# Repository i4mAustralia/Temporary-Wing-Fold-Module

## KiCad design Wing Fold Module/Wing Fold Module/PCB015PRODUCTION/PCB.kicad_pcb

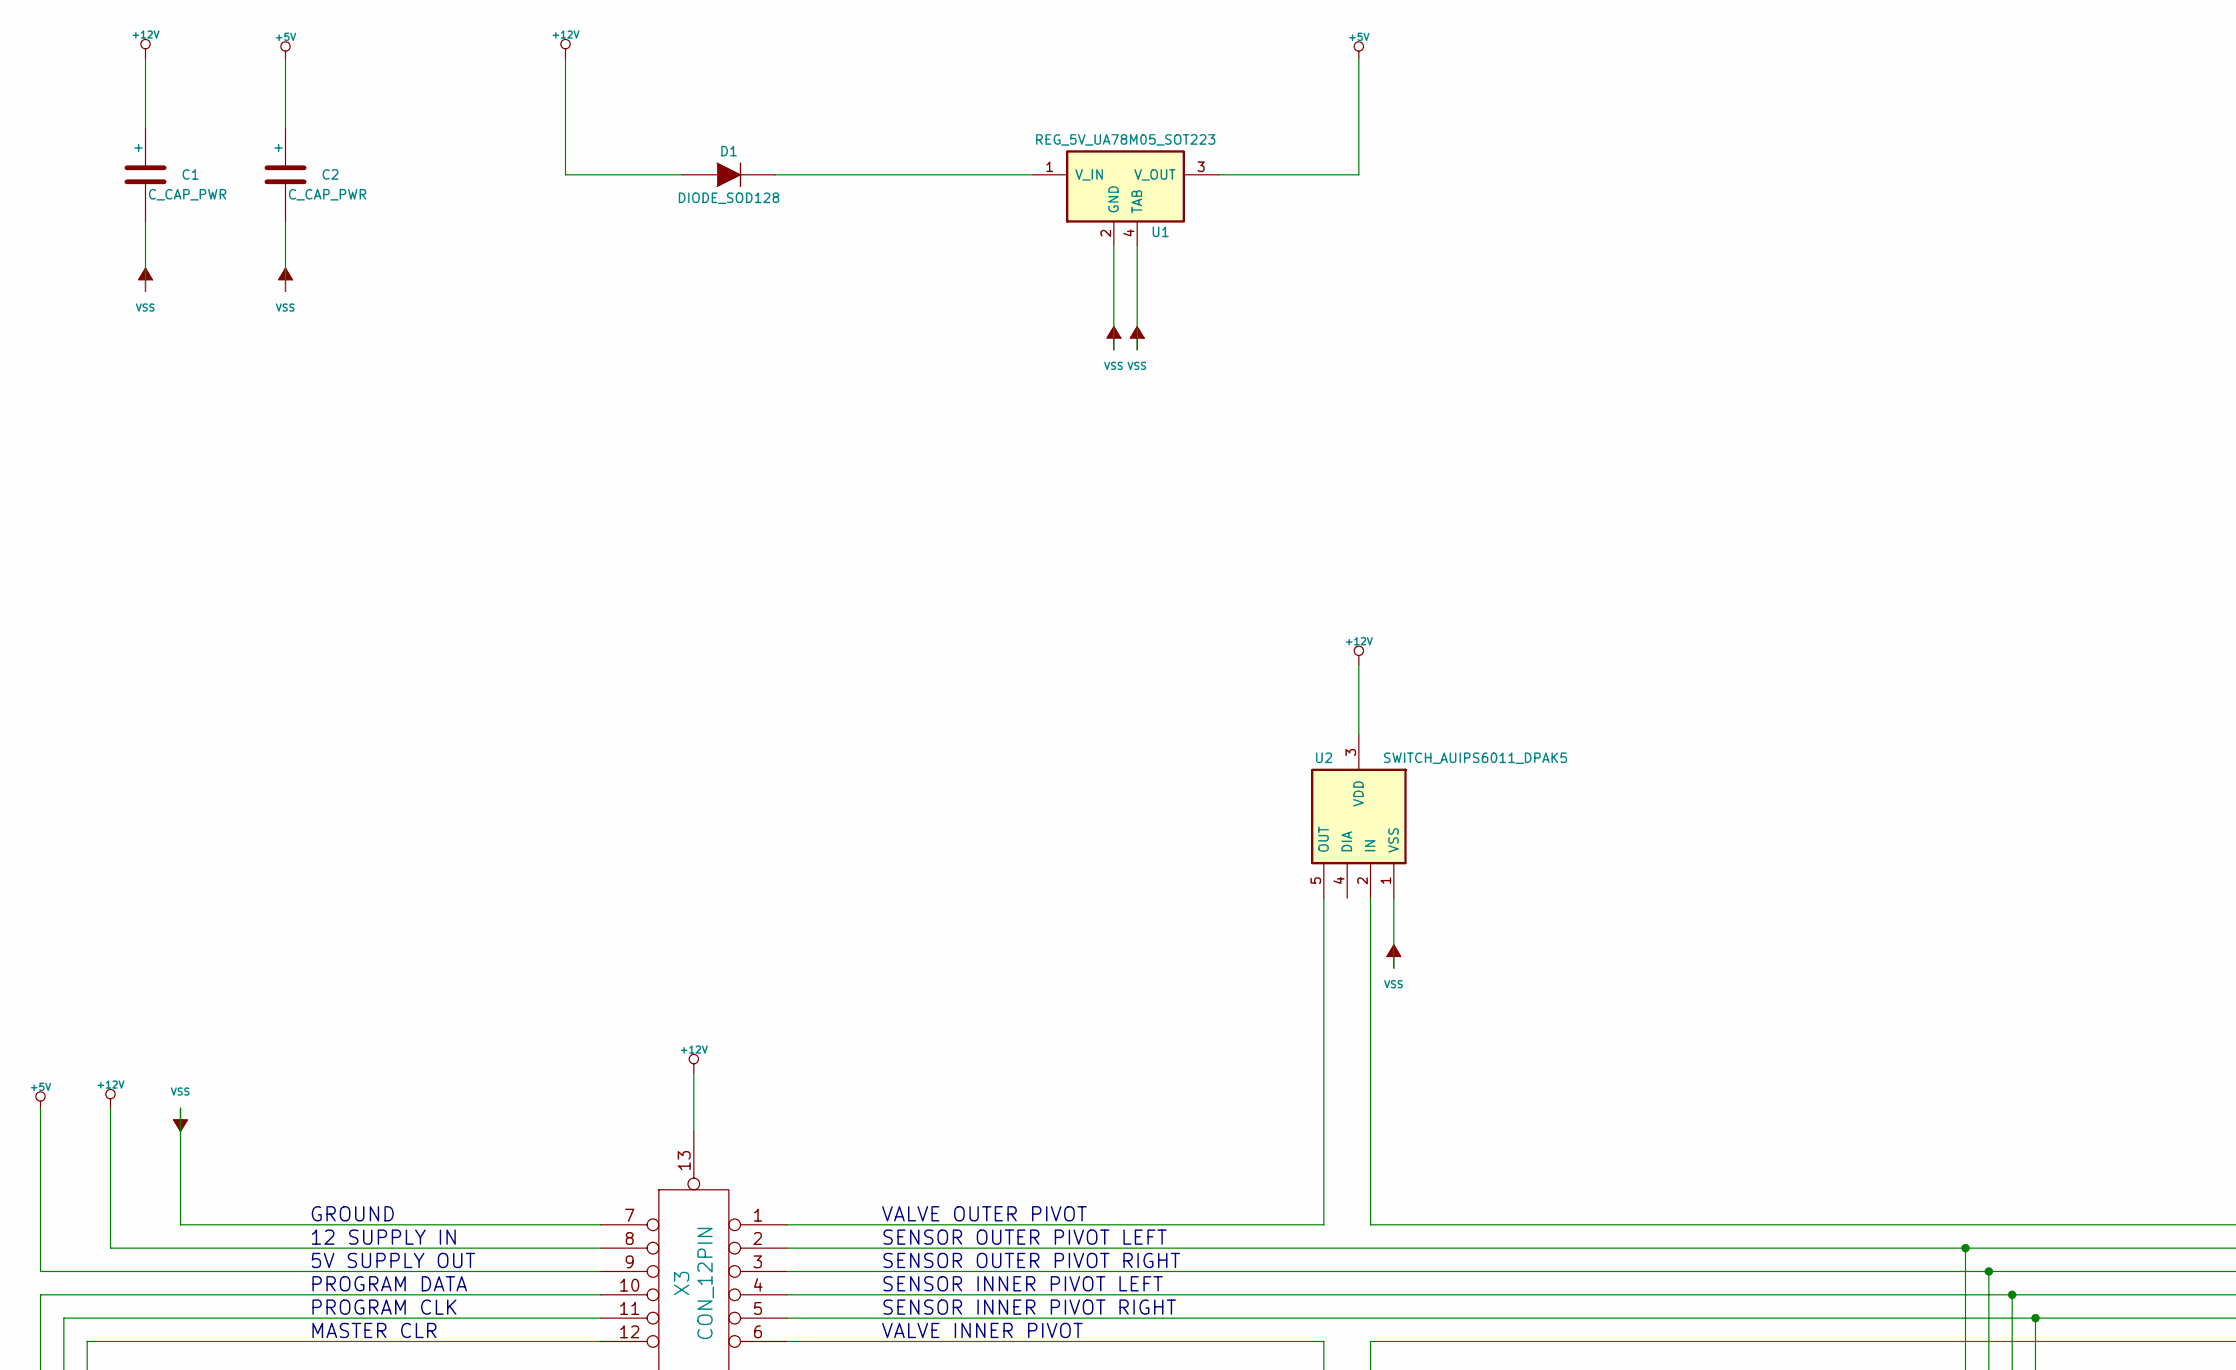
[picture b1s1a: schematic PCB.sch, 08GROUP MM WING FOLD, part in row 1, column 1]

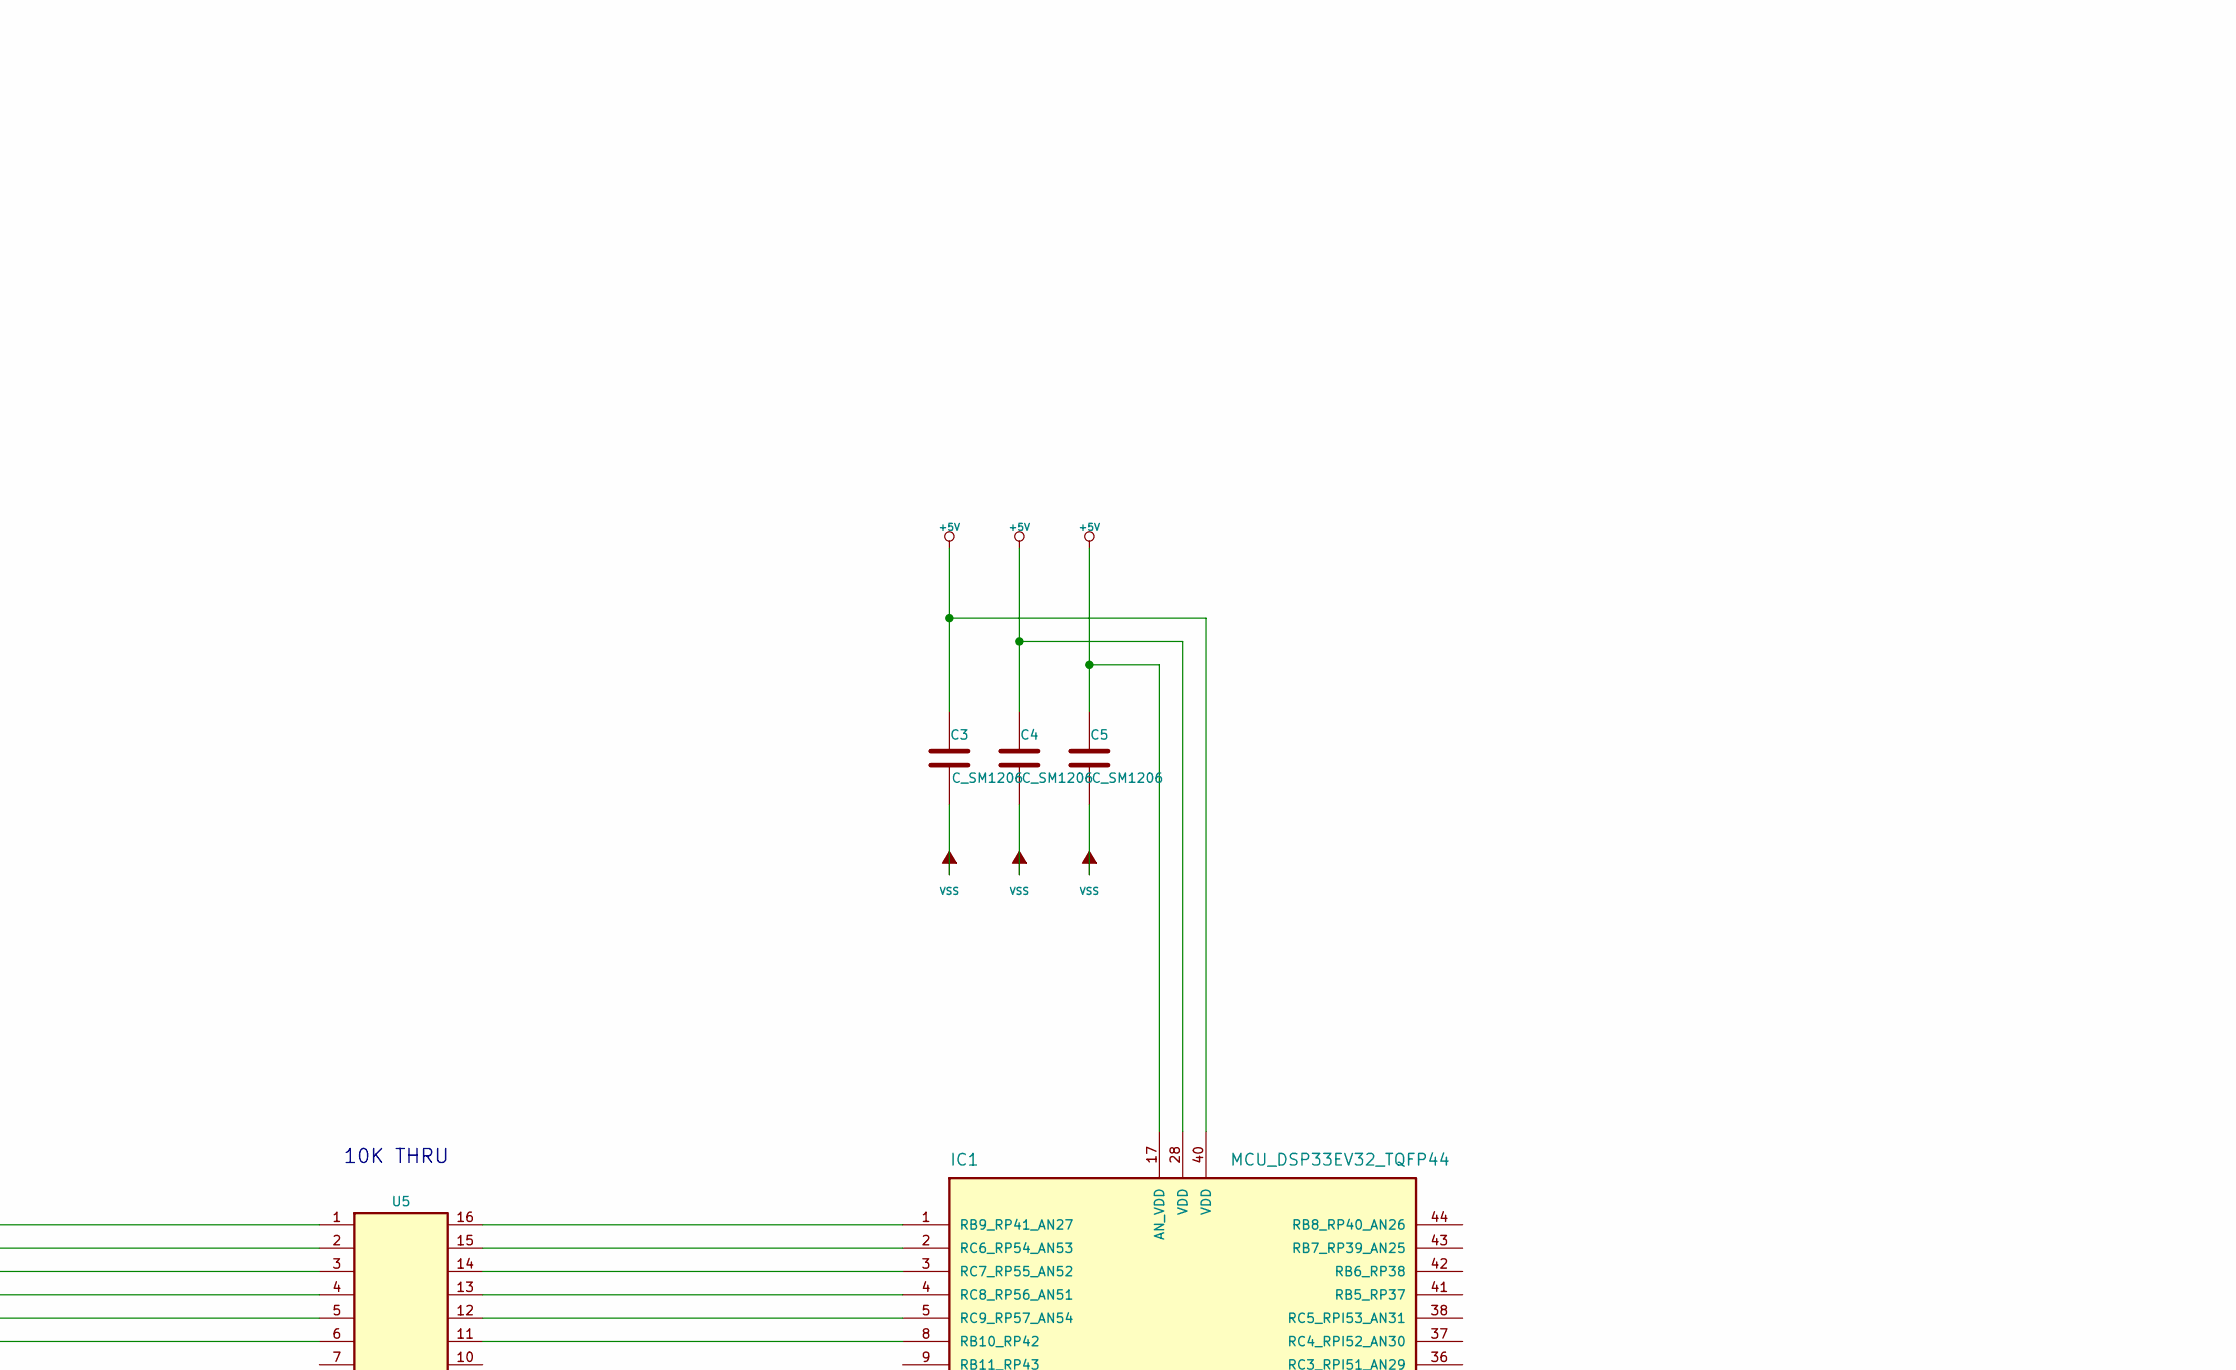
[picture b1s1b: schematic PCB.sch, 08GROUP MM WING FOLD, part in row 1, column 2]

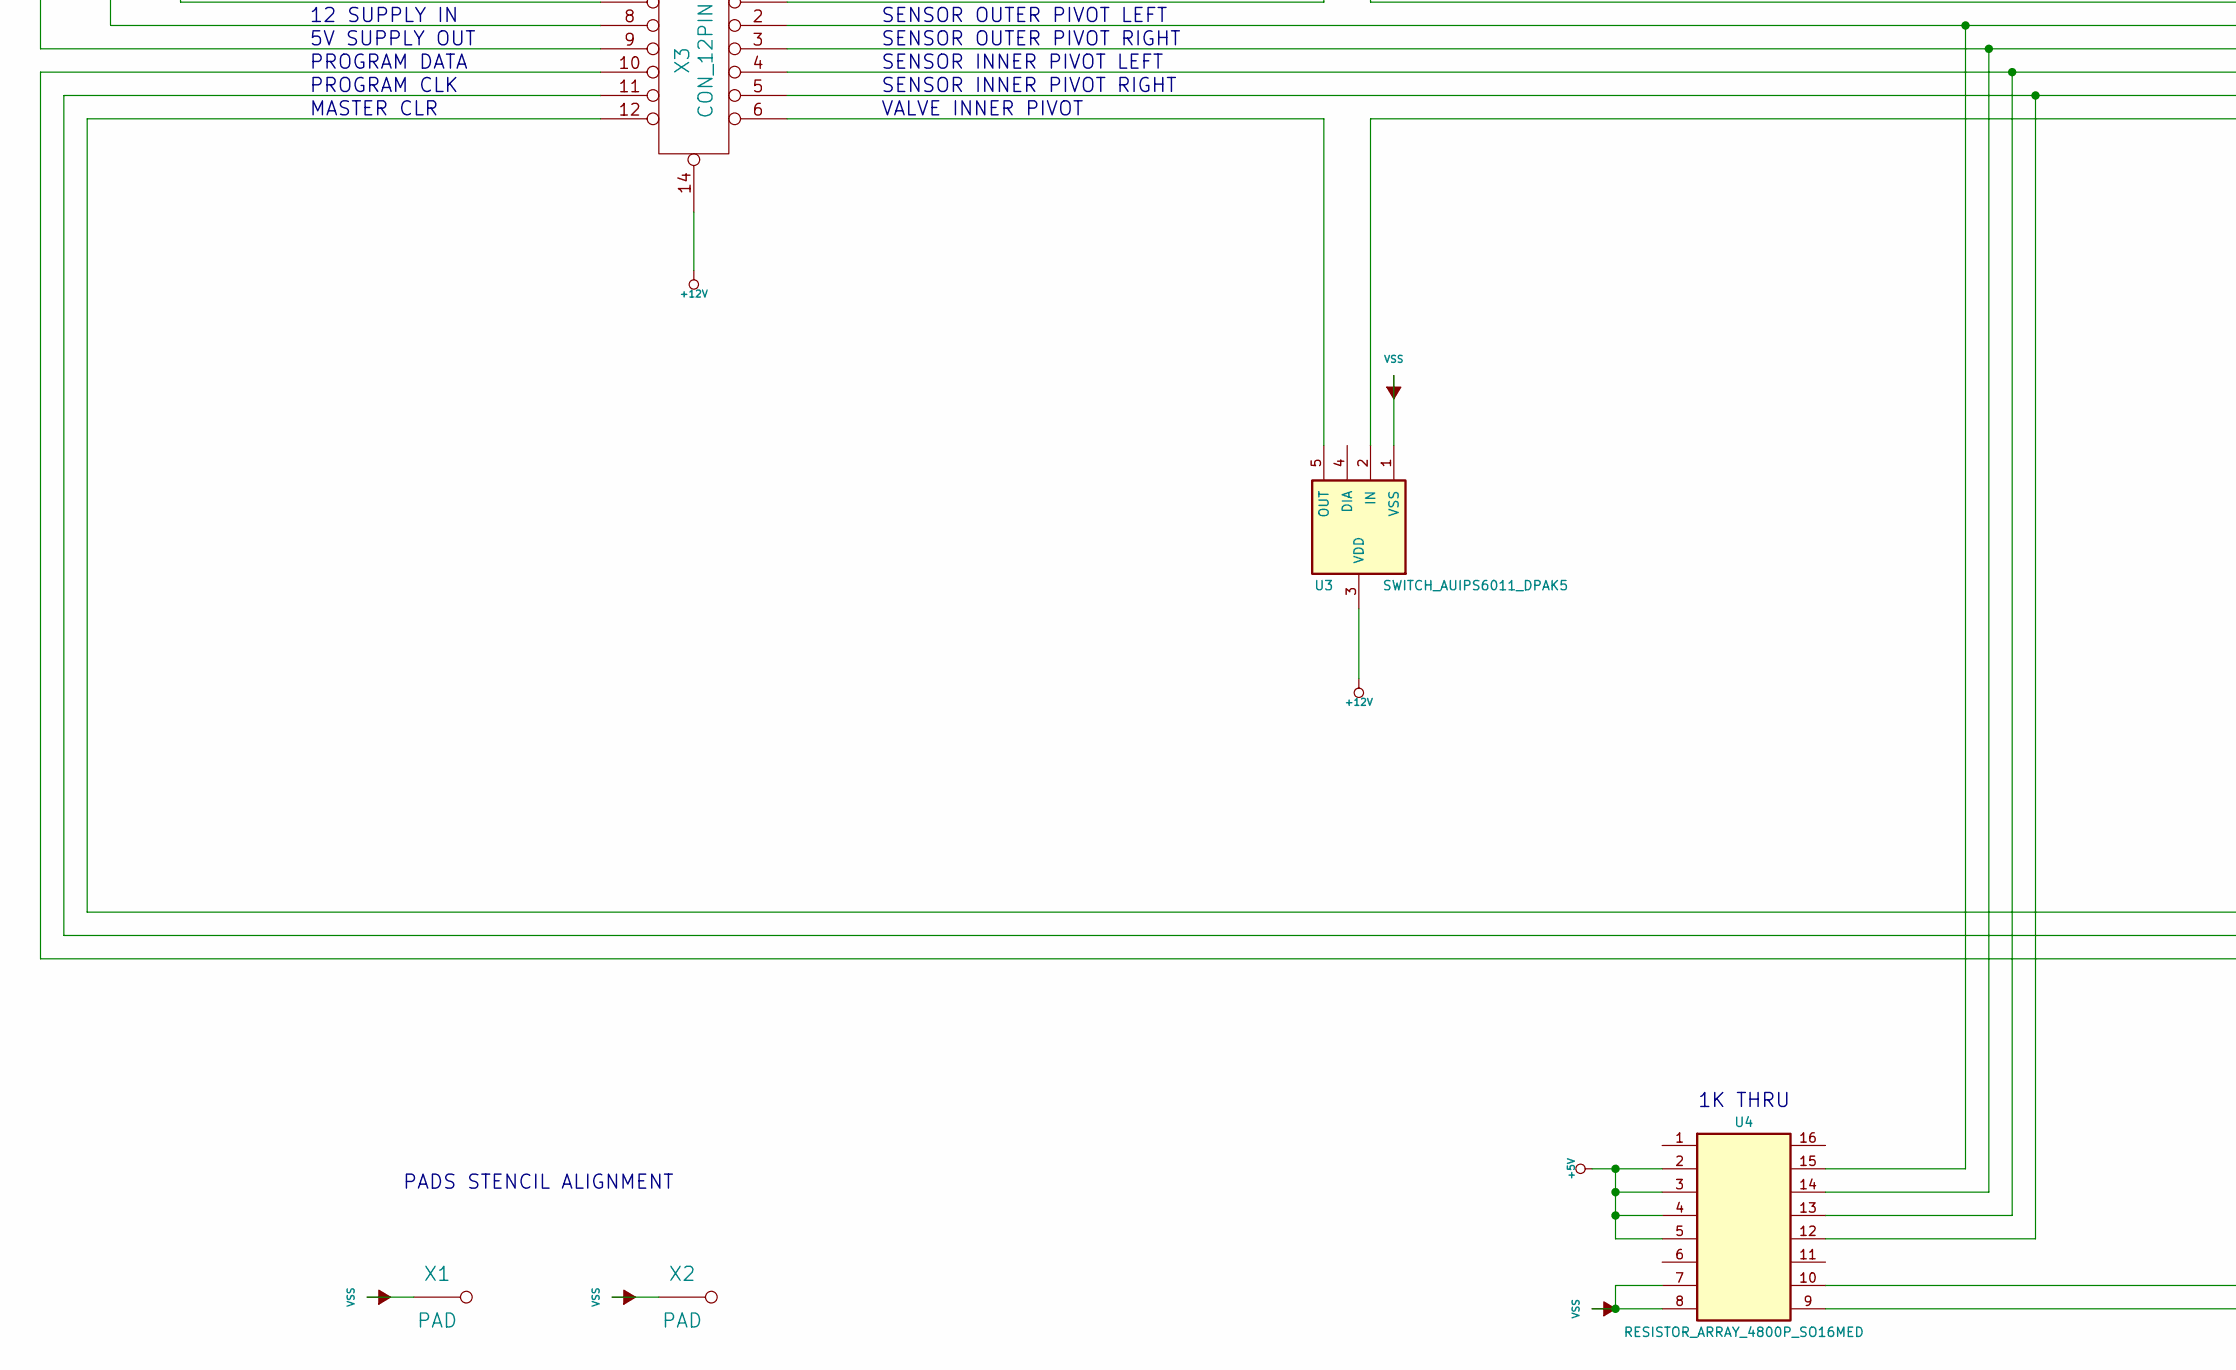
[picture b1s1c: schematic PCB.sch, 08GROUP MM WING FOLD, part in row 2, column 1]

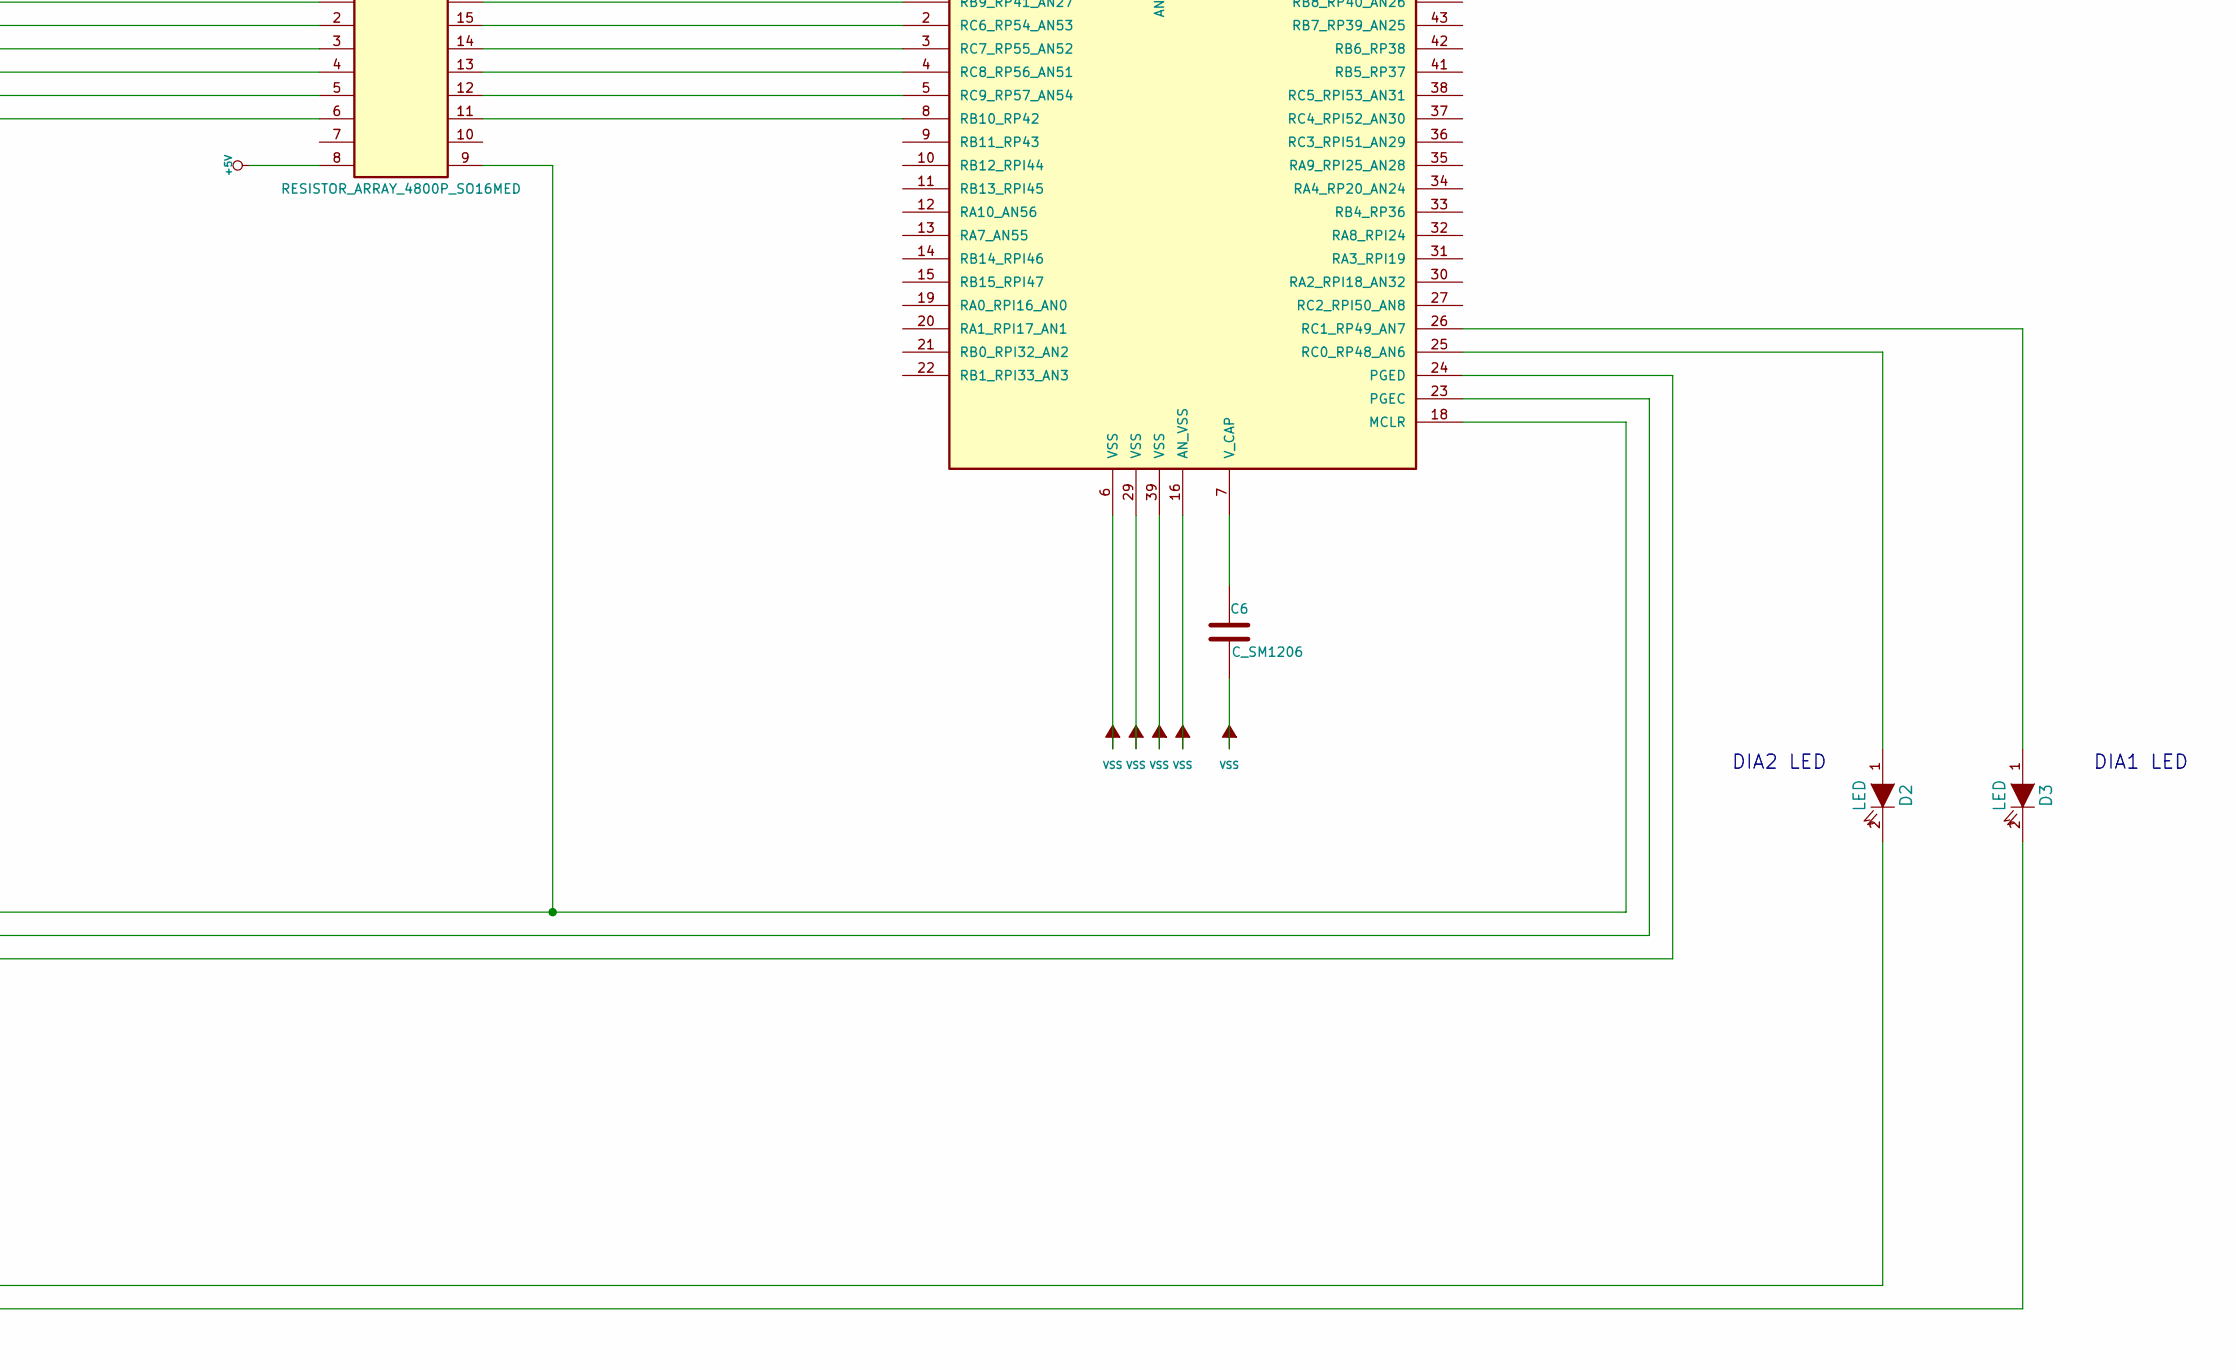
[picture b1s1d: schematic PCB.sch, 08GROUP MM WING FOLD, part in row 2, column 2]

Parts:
C1, C2: C_CAP_PWR
C3, C4, C5, C6: C_SM1206
D1: DIODE_SOD128
D2, D3: LED
IC1: MCU_DSP33EV32_TQFP44; TQFP100
U1: REG_5V_UA78M05_SOT223
U2, U3: SWITCH_AUIPS6011_DPAK5
U4, U5: RESISTOR_ARRAY_4800P_SO16MED
X1, X2: PAD
X3: CON_12PIN

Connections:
+5V: C2.1 (+), C3.1, C4.1, C5.1, IC1.17 (AN_VDD), IC1.28 (VDD), IC1.40 (VDD), U1.3 (V_OUT), U4.2, U4.3, U4.4, U4.5, U5.8, X3.9
+12V: C1.1 (+), D1.1 (A), U2.3 (VDD), U3.3 (VDD), X3.8, X3.13, X3.14
unnamed: IC1.3 (RC7_RP55_AN52), U5.14
unnamed: IC1.2 (RC6_RP54_AN53), U5.15
unnamed: IC1.1 (RB9_RP41_AN27), U5.16
unnamed: IC1.4 (RC8_RP56_AN51), U5.13
unnamed: IC1.18 (MCLR), U5.9, X3.12
unnamed: IC1.8 (RB10_RP42), U5.11
unnamed: IC1.5 (RC9_RP57_AN54), U5.12
unnamed: U3.2 (IN), U5.6
unnamed: U3.5 (OUT), X3.6
unnamed: U2.5 (OUT), X3.1
unnamed: U2.2 (IN), U5.1
unnamed: D1.2 (K), U1.1 (V_IN)
unnamed: D2.1 (A), IC1.25 (RC0_RP48_AN6)
unnamed: D3.2 (K), U4.9
unnamed: D2.2 (K), U4.10
unnamed: D3.1 (A), IC1.26 (RC1_RP49_AN7)
unnamed: IC1.23 (PGEC), X3.11
unnamed: U4.15, U5.2, X3.2
unnamed: U4.12, U5.5, X3.5
unnamed: U4.13, U5.4, X3.4
unnamed: U4.14, U5.3, X3.3
unnamed: IC1.24 (PGED), X3.10
unnamed: C6.1, IC1.7 (V_CAP)
VSS: C1.2, C2.2, C3.2, C4.2, C5.2, C6.2, IC1.6 (VSS), IC1.16 (AN_VSS), IC1.29 (VSS), IC1.39 (VSS), U1.2 (GND), U1.4 (TAB), U2.1 (VSS), U3.1 (VSS), U4.7, U4.8, X1.1, X2.1, X3.7

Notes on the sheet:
PADS STENCIL ALIGNMENT
10K THRU
1K THRU
VALVE OUTER PIVOT
VALVE INNER PIVOT
SENSOR INNER PIVOT RIGHT
SENSOR INNER PIVOT LEFT
SENSOR OUTER PIVOT LEFT
SENSOR OUTER PIVOT RIGHT
12 SUPPLY IN
5V SUPPLY OUT
GROUND
MASTER CLR
PROGRAM DATA
PROGRAM CLK
DIA1 LED
DIA2 LED

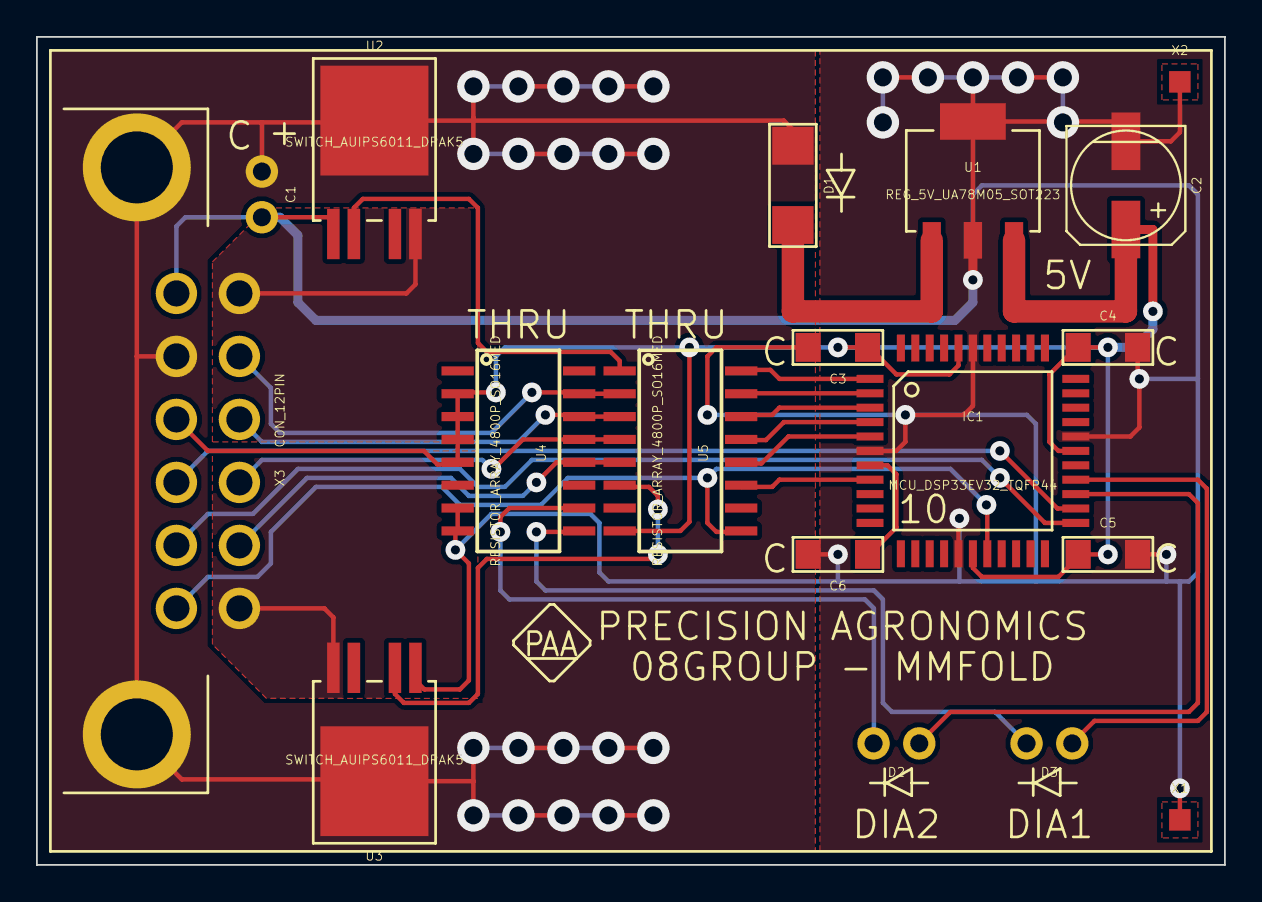
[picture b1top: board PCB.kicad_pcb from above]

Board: 2 copper layers, 66.0 x 46.0 mm, 18 parts (0 on the bottom side), 26 nets.

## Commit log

2021-10-15 updating libraries

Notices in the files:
Wing Fold Module/Wing Fold Module/PCB015PRODUCTION/PCB.sch:
Copyright © Not to be used or distributed without written approval.
